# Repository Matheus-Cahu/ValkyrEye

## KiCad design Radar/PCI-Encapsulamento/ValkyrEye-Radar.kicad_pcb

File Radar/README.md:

# Radar

## Sketches disponíveis

- `ScannerLoRa.ino`: leitura do HC-SR04 com servo e envio dos alertas LoRa.
- [receptor](receptor/README.md): central integrada, recebe os alertas LoRa,
  imprime-os na serial e envia as leituras reais à API por Wi-Fi/HTTP.
- [WiFiConnection](Conexoes/WiFi/README.md): teste de conexão e envio de dados
  simulados à API.

Para a central conectada à plataforma, carregue o sketch
`receptor/receptor.ino`. Cada sketch deve ser compilado
separadamente; o arquivo ScannerLoRa na raiz precisa ficar
em uma pasta de mesmo nome quando abertos como projetos na IDE do Arduino.

Firmware dos pontos de detecção (ESP32 LoRa, HC-SR04 e servo) e da central
receptora LoRa. O [contrato lógico do alerta](../docs/ARQUITETURA.md) define os
campos que devem chegar ao Raspberry Pi.

Primeira entrega: medir e filtrar distâncias, calibrar o ângulo do servo,
transmitir alertas com número de sequência e confirmar o recebimento na central.

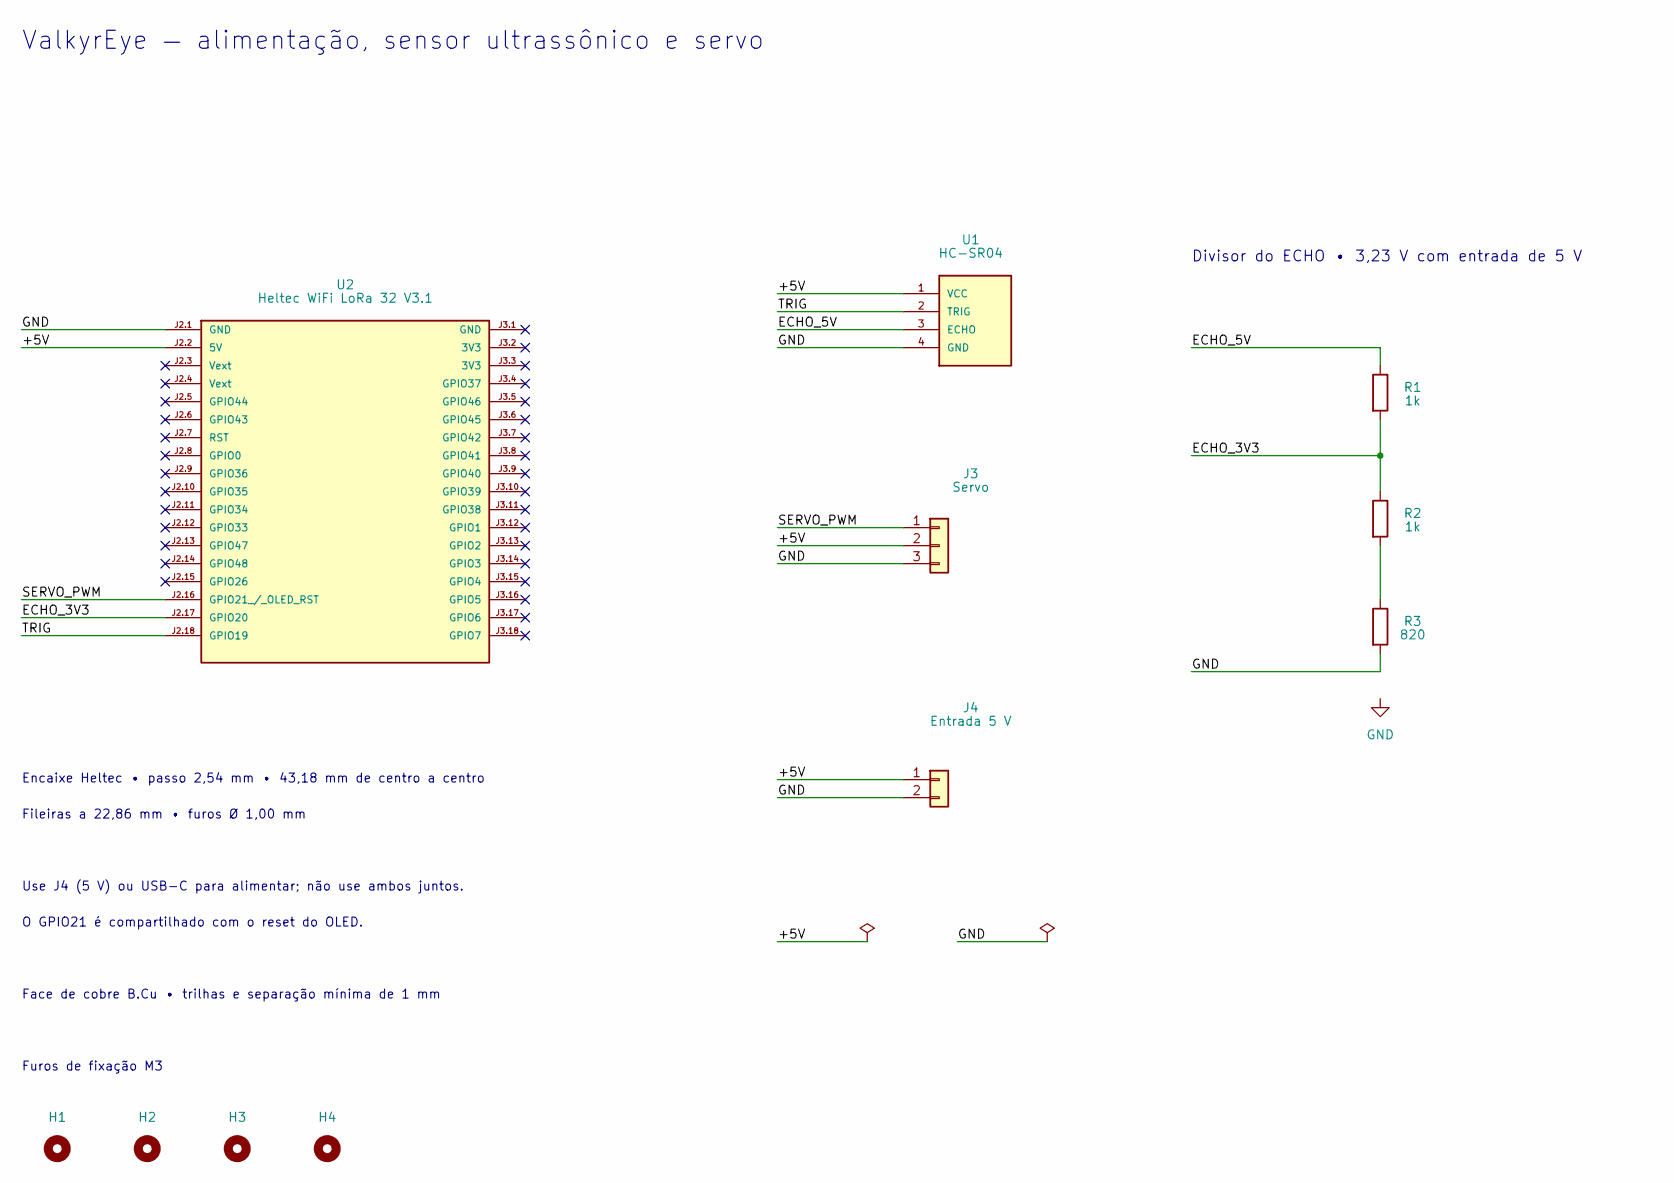
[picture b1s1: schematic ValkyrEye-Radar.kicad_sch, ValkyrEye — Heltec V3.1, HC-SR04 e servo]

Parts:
H1, H2, H3, H4: Furo M3; MountingHole_3.2mm_M3
J3: Servo; Servo_1x03_P2.54mm
J4: Entrada 5 V; Entrada_1x02_P5.08mm
R1, R2: 1k; Resistor_Axial_P7.62mm
R3: 820; Resistor_Axial_P7.62mm
U1: HC-SR04; XCVR_HC-SR04
U2: Heltec WiFi LoRa 32 V3.1; Heltec_WiFi_LoRa_32_V3_1

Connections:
/+5V: J3.2, J4.1, U1.1 (VCC), U2.J2.2 (5V)
/ECHO_3V3: R1.2, R2.1, U2.J2.17 (GPIO20)
/ECHO_5V: R1.1, U1.3 (ECHO)
/SERVO_PWM: J3.1, U2.J2.16 (GPIO21_/_OLED_RST)
/TRIG: U1.2 (TRIG), U2.J2.18 (GPIO19)
GND: J3.3, J4.2, R3.2, U1.4 (GND), U2.J2.1 (GND)
unnamed: R2.2, R3.1

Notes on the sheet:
Use J4 (5 V) ou USB-C para alimentar; não use ambos juntos.
O GPIO21 é compartilhado com o reset do OLED.
Fileiras a 22,86 mm • furos Ø 1,00 mm
Divisor do ECHO • 3,23 V com entrada de 5 V
Face de cobre B.Cu • trilhas e separação mínima de 1 mm
Furos de fixação M3
ValkyrEye — alimentação, sensor ultrassônico e servo
Encaixe Heltec • passo 2,54 mm • 43,18 mm de centro a centro

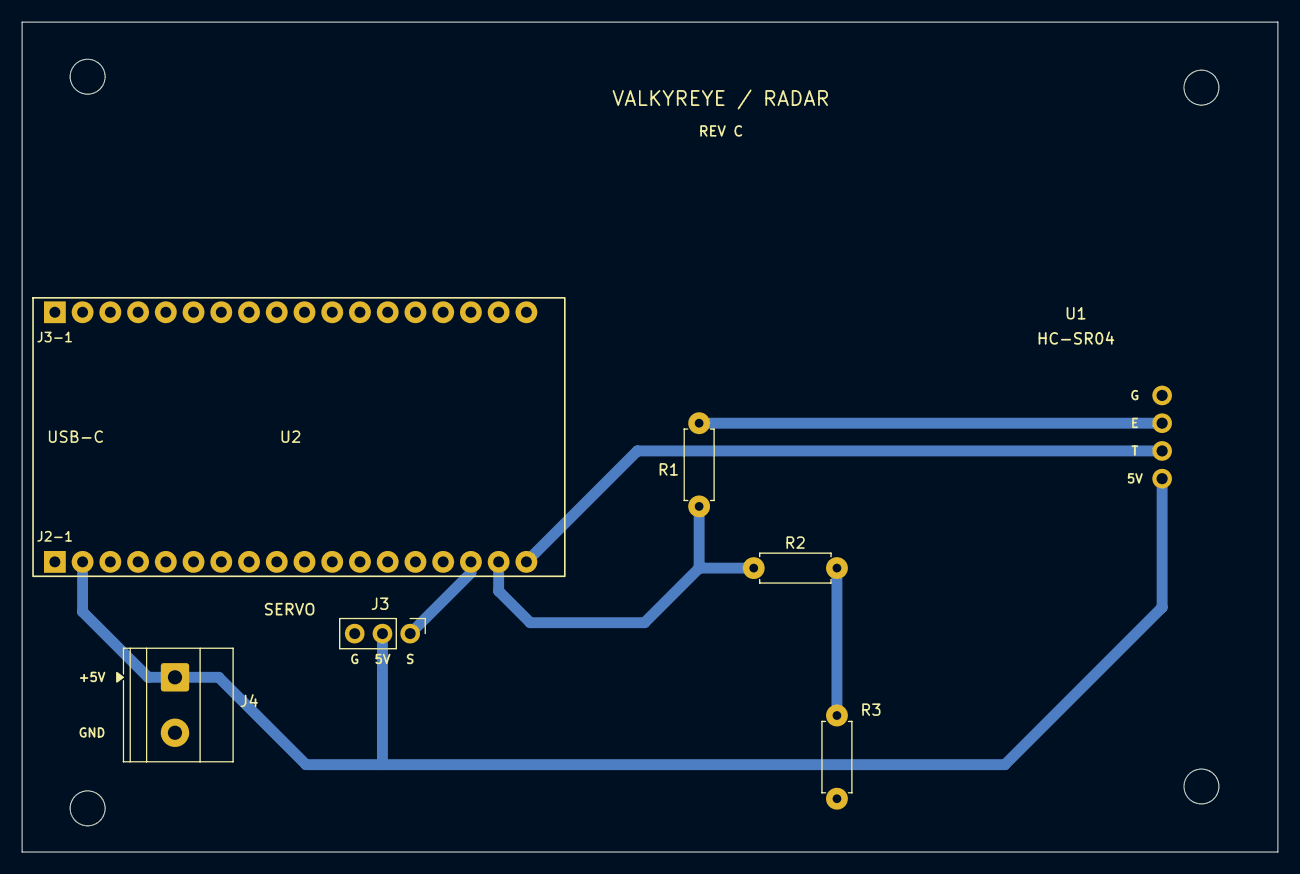
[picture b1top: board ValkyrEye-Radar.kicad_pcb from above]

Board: 2 copper layers, 115.0 x 76.0 mm, 11 parts (0 on the bottom side), 7 nets.
